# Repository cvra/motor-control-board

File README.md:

CVRA DC-Motor Controller
========================

Features:
---------

 - CAN interface
 - DC motor control with current sensing
 - Quadrature encoder interface for motor (5V tolerant)
 - Secondary quadrature encoder interface (5V tolerant) (eg. for separate odometry wheels)
 - Analog input for RC-servo control
 - Runs on 3 or 4 cell LiPo batteries

License
-------
This project is released under the Creative Commons CC-BY-SA-4.0 license.
See http://creativecommons.org/licenses/by-sa/4.0/ for details.

Assembly
--------

# Applying solder paste

 - This needs 2 persons.
 - Solder paste and stencil need to be _cold_ (couple of minutes in the fridge)
 - Use the 3D printed frames. Stick them to the table with double sided tape
    and stick the PCB to the frame with small pieces of double sided tape.
    If you don't do this, the PCB will stick to the sencil when you try to remove it.
 - To remove the stencil, rotate it around one of the short edges, to pull it
   as perpendicular as possible with the least amount of shaking.
 - Move the PCB with the applied solder paste to a frame without double sided
   tape before assembling the parts, because they would probably flick off.
 - Check the footprints with the smallest pitch under the microscope for bad
   alignment and if the brim is nice (if it isn't, the paste was probably too warm).

# Assembling the parts
 - Remove the solder paste on the NC pad of the voltage regulator with the wrong
   footprint.
 - Use the vacuum pump for larger parts and tweezers for smaller ones.

# Baking

 - Preheat the frame made out of plaster to >200°C, else it won't reflow!
 - Move the PCB to the plaster frame.
 - Put the frame and the thermal probe in the furnace. Take care that you don't
   accidentally move any parts by touching them with the probe.
 - Heat until the solder paste starts to liquidify (shouldn't be more than
   ~230°C; never go higher than 250°C).
 - Keep the peak temperature for about a minute.
 - Open the furnace door a little bit to slowly cool down the PCBs.
 - Don't remove the PCB from the furnace before it's colder than ~70°C.

# Flashing and testing

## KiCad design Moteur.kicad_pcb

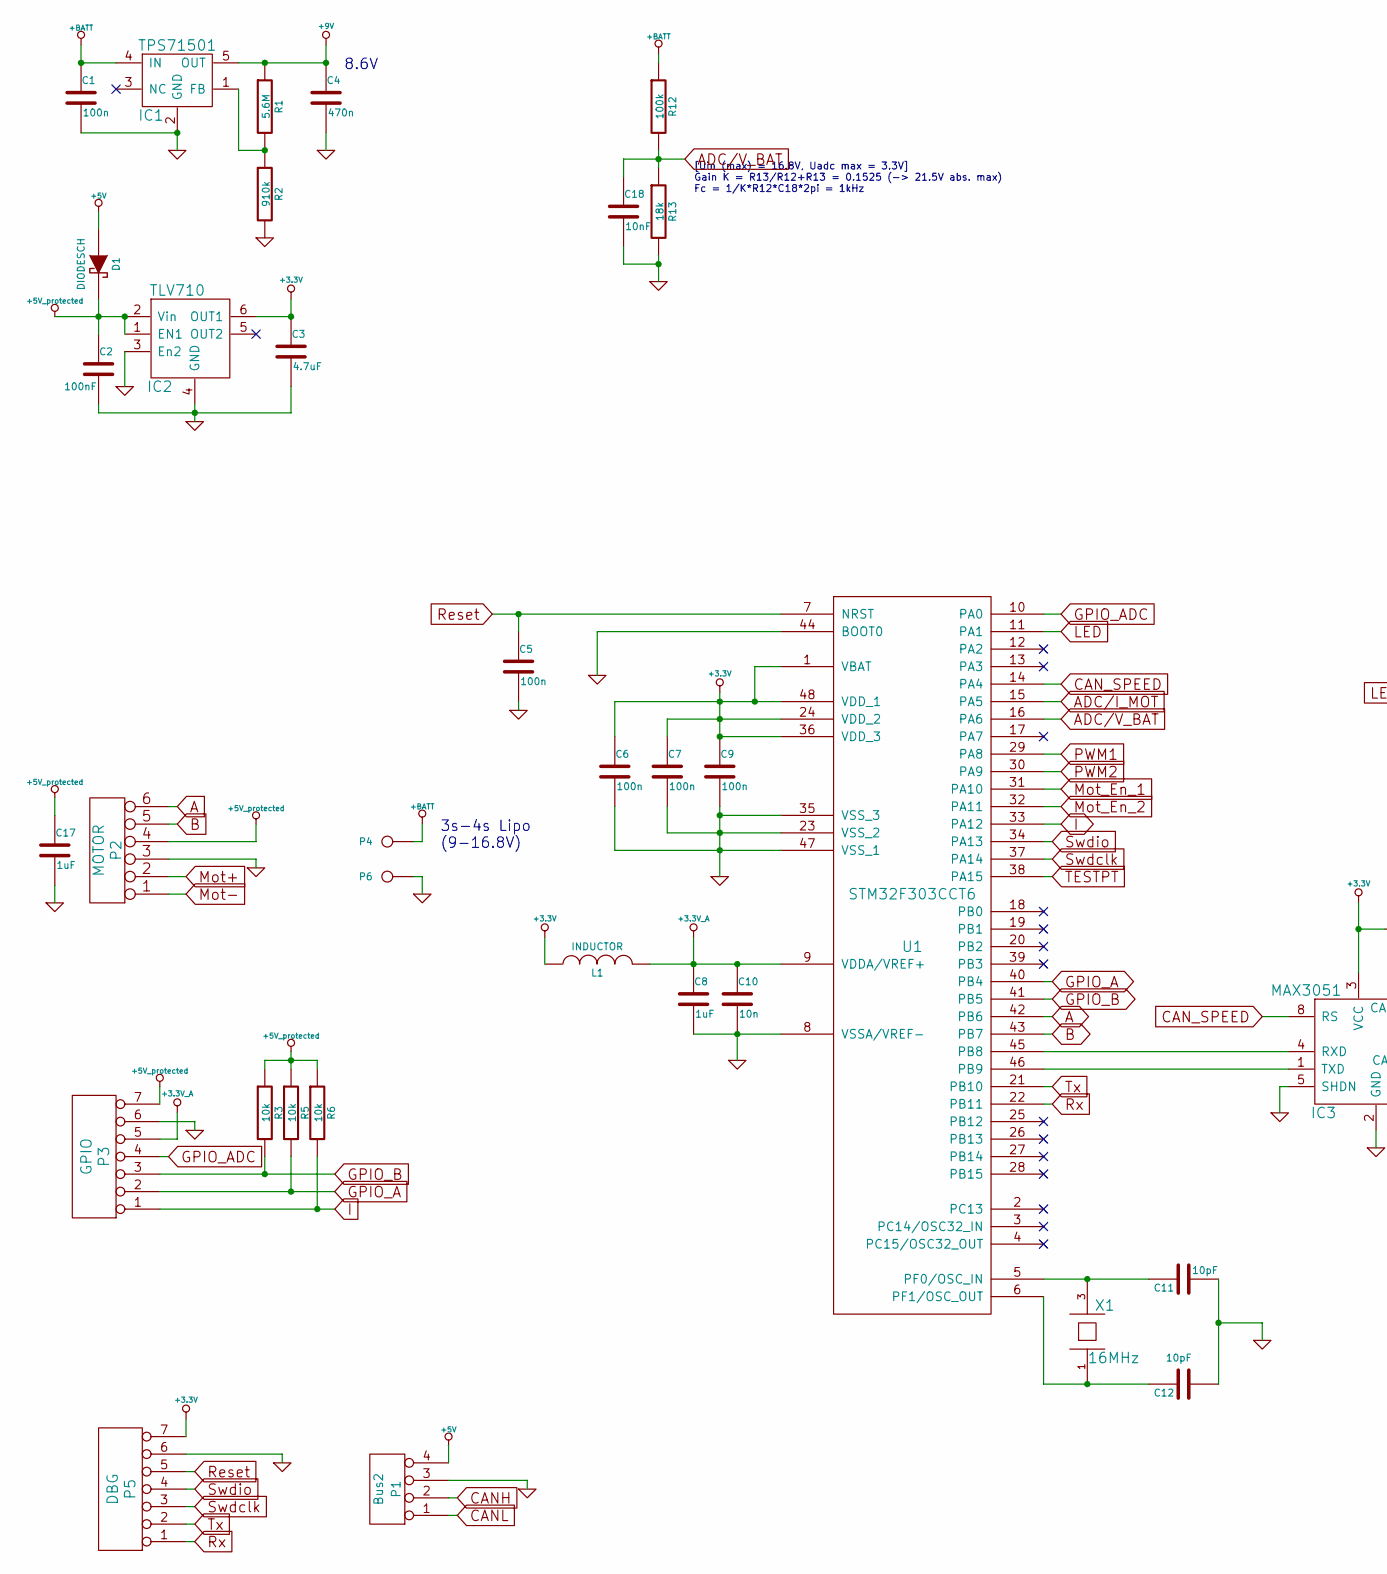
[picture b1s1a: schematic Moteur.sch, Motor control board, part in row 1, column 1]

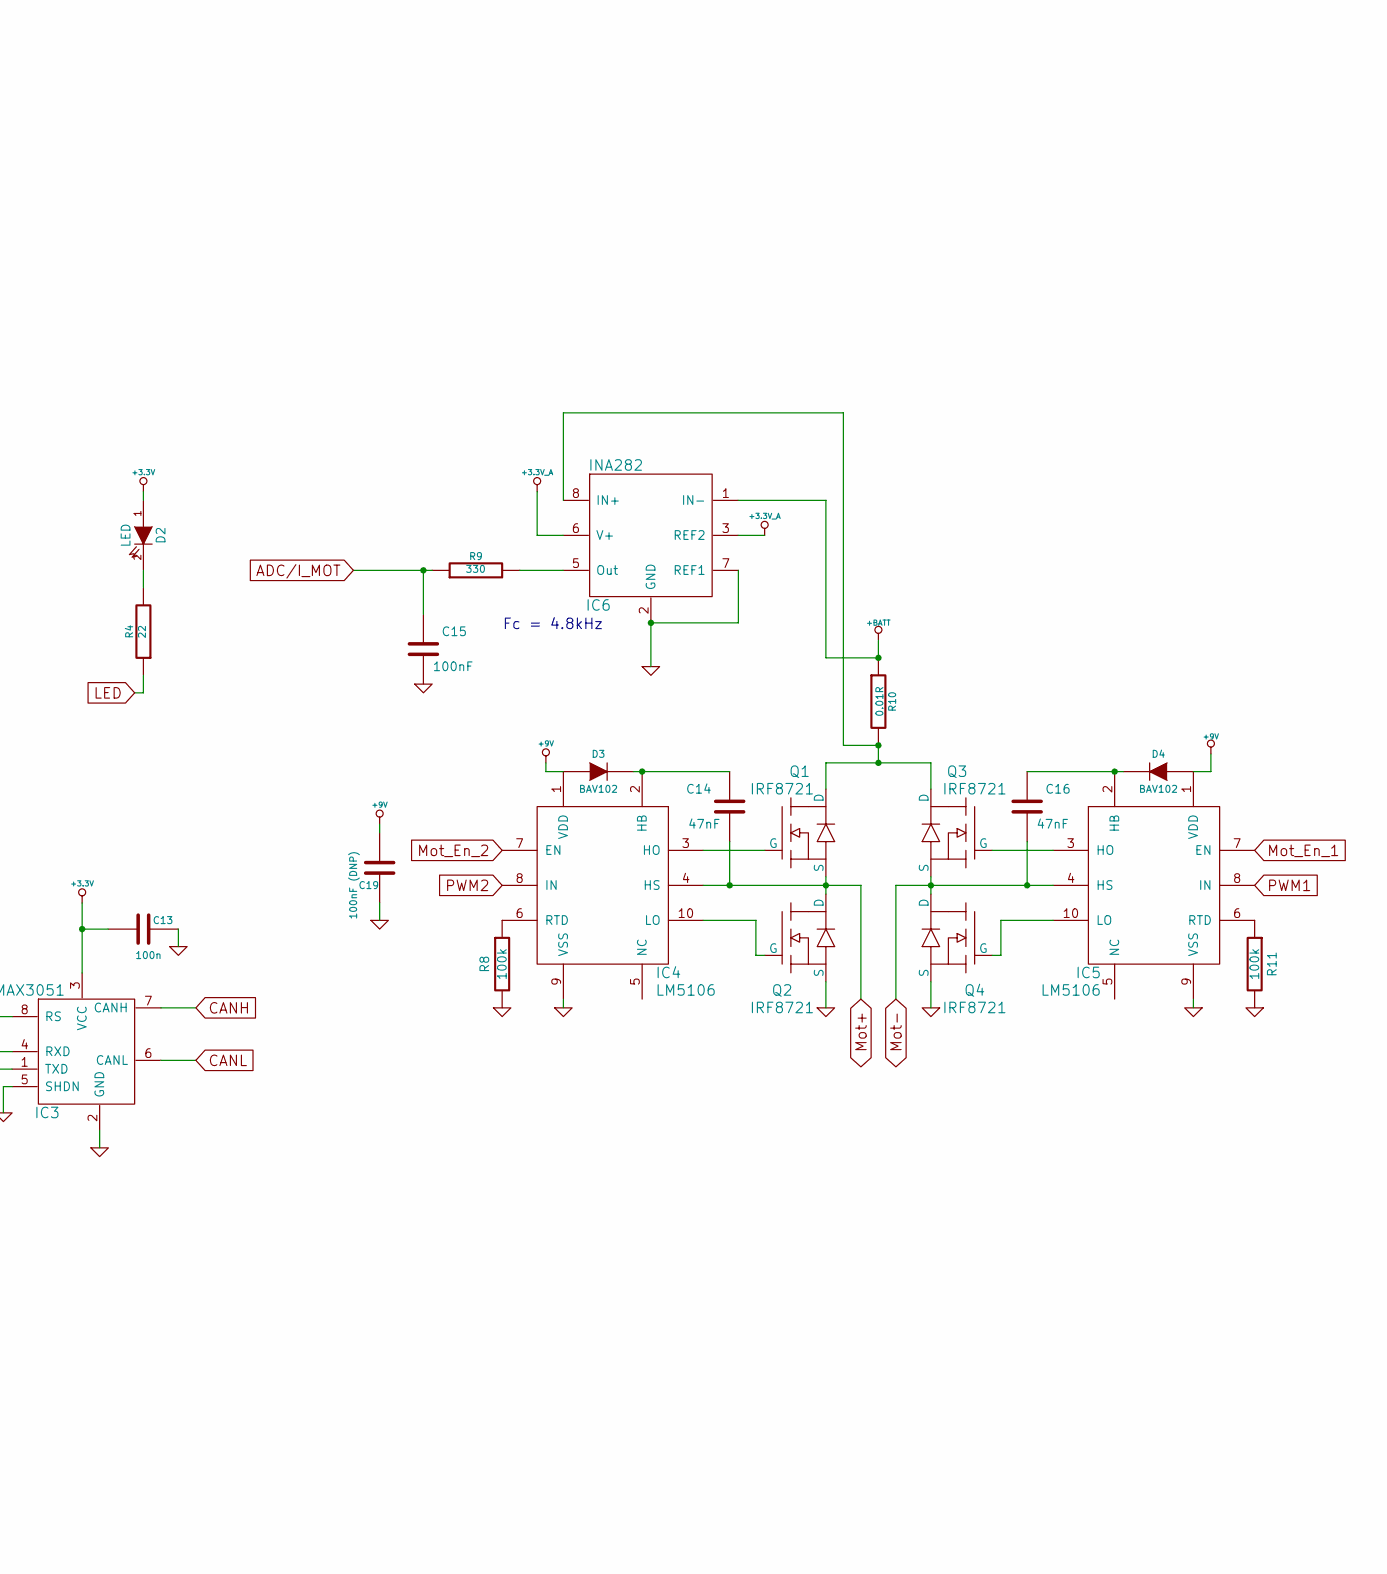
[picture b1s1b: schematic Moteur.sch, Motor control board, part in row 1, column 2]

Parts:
C1, C5, C6, C7, C9, C13: 100n
C2: 100nF
C3: 4.7uF
C4: 470n
C8, C17: 1uF
C10: 10n
C11, C12: 10pF
C14, C16: 47nF; SM1206
C15: 100nF; SM1206
C18: 10nF
C19: 100nF (DNP)
D1: DIODESCH
D2: LED
D3, D4: BAV102; diode-1-SOD80C
IC1: TPS71501
IC2: TLV710
IC3: MAX3051
IC4, IC5: LM5106
IC6: INA282
L1: INDUCTOR
P1: Bus2
P2: MOTOR
P3: GPIO
P4, P6: CONN_1
P5: DBG
Q1, Q2, Q3, Q4: IRF8721; transistor-power-SOT669
R1: 5.6M
R2: 910k
R3, R5, R6: 10k
R4: 22
R8, R11: 100k; SM0805
R9: 330
R10: 0.01R
R12: 100k
R13: 18k
U1: STM32F303CCT6; MODULE
X1: 16MHz

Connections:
+3.3V: C3.1, C6.1, C7.1, C9.1, C13.2, D2.1 (A), IC2.6 (OUT1), IC3.3 (VCC), L1.1, P5.7, U1.1 (VBAT), U1.24 (VDD_2), U1.36 (VDD_3), U1.48 (VDD_1)
+3.3V_A: C8.1, C10.1, IC6.3 (REF2), IC6.6 (V+), L1.2, P3.5, U1.9 (VDDA/VREF+)
+5V: D1.1 (A), P1.4
+5V_protected: C2.1, C17.1, D1.2 (K), IC2.1 (EN1), IC2.2 (Vin), P2.4, P3.7, R3.1, R5.1, R6.1
+9V: C4.1, C19.2, D3.1 (A), D4.1 (A), IC1.5 (OUT), IC4.1 (VDD), IC5.1 (VDD), R1.1
+BATT: C1.1, IC1.4 (IN), IC6.1 (IN-), P4.1, R10.1, R12.1
A: P2.6, U1.42 (PB6)
ADC/I_MOT: C15.1, R9.1, U1.15 (PA5)
ADC/V_BAT: C18.1, R12.2, R13.1, U1.16 (PA6)
B: P2.5, U1.43 (PB7)
CANH: IC3.7 (CANH), P1.2
CANL: IC3.6 (CANL), P1.1
CAN_SPEED: IC3.8 (RS), U1.14 (PA4)
GND: C1.2, C2.2, C3.2, C4.2, C5.2, C6.2, C7.2, C8.2, C9.2, C10.2, C11.2, C12.2, C13.1, C15.2, C17.2, C18.2, C19.1, IC1.2 (GND), IC2.3 (En2), IC2.4 (GND), IC3.2 (GND), IC3.5 (SHDN), IC4.9 (VSS), IC5.9 (VSS), IC6.2 (GND), IC6.7 (REF1), P1.3, P2.3, P3.6, P5.6, P6.1, Q2.1 (S), Q2.2, Q2.3, Q4.1 (S), Q4.2, Q4.3, R2.2, R8.2, R11.2, R13.2, U1.8 (VSSA/VREF-), U1.23 (VSS_2), U1.35 (VSS_3), U1.44 (BOOT0), U1.47 (VSS_1)
GPIO_A: P3.2, R5.2, U1.40 (PB4)
GPIO_ADC: P3.4, U1.10 (PA0)
GPIO_B: P3.3, R3.2, U1.41 (PB5)
I: P3.1, R6.2, U1.33 (PA12)
LED: R4.1, U1.11 (PA1)
Mot+: C14.2, IC4.4 (HS), P2.2, Q1.1 (S), Q1.2, Q1.3, Q2.5 (D), Q2.6, Q2.7, Q2.8
Mot-: C16.2, IC5.4 (HS), P2.1, Q3.1 (S), Q3.2, Q3.3, Q4.5 (D), Q4.6, Q4.7, Q4.8
Mot_En_1: IC5.7 (EN), U1.31 (PA10)
Mot_En_2: IC4.7 (EN), U1.32 (PA11)
unnamed: C11.1, U1.5 (PF0/OSC_IN), X1.3
unnamed: C12.1, U1.6 (PF1/OSC_OUT), X1.1
unnamed: C14.1, D3.2 (K), IC4.2 (HB)
unnamed: C16.1, D4.2 (K), IC5.2 (HB)
unnamed: D2.2 (K), R4.2
unnamed: IC1.1 (FB), R1.2, R2.1
unnamed: IC3.1 (TXD), U1.46 (PB9)
unnamed: IC3.4 (RXD), U1.45 (PB8)
unnamed: IC4.3 (HO), Q1.4 (G)
unnamed: IC4.6 (RTD), R8.1
unnamed: IC4.10 (LO), Q2.4 (G)
unnamed: IC5.3 (HO), Q3.4 (G)
unnamed: IC5.6 (RTD), R11.1
unnamed: IC5.10 (LO), Q4.4 (G)
unnamed: IC6.5 (Out), R9.2
unnamed: IC6.8 (IN+), Q1.5 (D), Q1.6, Q1.7, Q1.8, Q3.5 (D), Q3.6, Q3.7, Q3.8, R10.2
PWM1: IC5.8 (IN), U1.29 (PA8)
PWM2: IC4.8 (IN), U1.30 (PA9)
Reset: C5.1, P5.5, U1.7 (NRST)
Rx: P5.1, U1.22 (PB11)
Swdclk: P5.3, U1.37 (PA14)
Swdio: P5.4, U1.34 (PA13)
TESTPT: U1.38 (PA15)
Tx: P5.2, U1.21 (PB10)

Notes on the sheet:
Fc = 4.8kHz
[Uin (max) = 16.8V, Uadc max = 3.3V] Gain K = R13/R12+R13 = 0.1525 (-> 21.5V abs. max) Fc = 1/K*R12*C18*2pi = 1kHz
3s-4s Lipo (9-16.8V)
8.6V

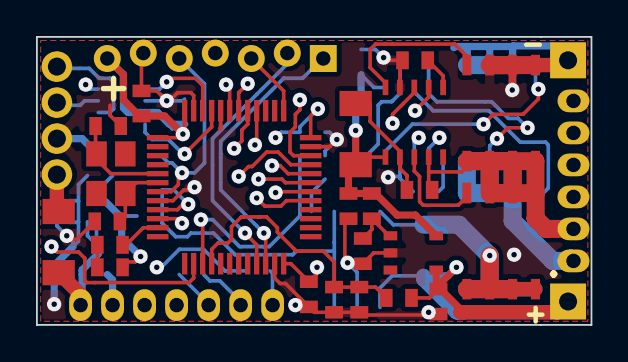
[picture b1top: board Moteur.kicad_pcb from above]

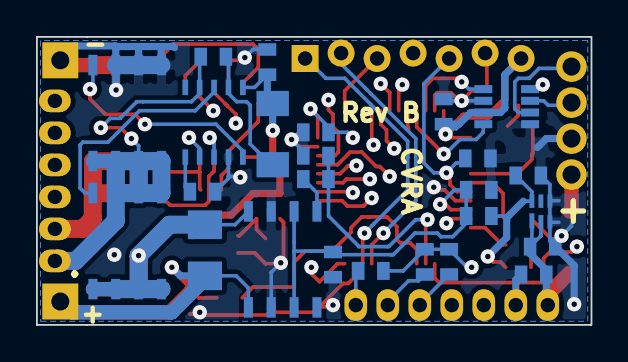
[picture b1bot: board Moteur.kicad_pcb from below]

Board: 4 copper layers, 30.8 x 16.0 mm, 54 parts (26 on the bottom side), 46 nets.

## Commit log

2014-10-31 add kicad lib submodule
2014-10-31 add cache
2014-10-31 gitignore
2014-10-31 add all libs
2014-10-31 add correct stm32 symbol
2014-10-31 add pinout
2014-11-05 design review
2014-11-05 update submodule url
2014-11-05 update library path
2014-11-05 Add something useless
2014-11-05 remove something useless
2014-11-05 Update the library with the most beautiful symbol EVER EVER EVER !
2014-11-05 update current measurement filter, fix connection CAN termination resistor
2014-11-05 power supply minor fixes
2014-11-09 Schéma Complet
2014-11-10 Add datasheet folder
2014-11-12 Couche PCB Définie
2014-11-13 minor schematic fixes, start assigning footprints
2014-11-13 footprints assignment
2014-11-13 connect encoders to diode protected 5V
2014-11-13 add V_Bat resistive divider for ADC
2014-11-13 remove nonexistent libs, add cvra lib
2014-11-13 Fix 5V protected symbol name
    Apparently KiCAD has case sensitive symbol names... nice
2014-11-13 change submodule from ssh to https
2014-11-15 Add Diode
2014-11-15 Boitier Choisi
2014-11-16 Set footprint for TLV710 and LM5106 Corrected footprint for shunt resistor
2014-11-19 update lib
2014-11-19 footprints
2014-11-22 Update footprint link, disperse component on PCB and add pcb size
2014-11-23 Add board outline and placed power stage
2014-11-23 Placement driver can
2014-11-26 fix labels, pinout
2014-11-26 final schematic review, component placement
2014-11-27 placement
2014-11-27 component placement
2014-11-28 add GND to GPIO connector, exchange CANL,CANH
2014-11-28 optimize placement
2014-11-28 add new gpio connector with gnd
2014-12-02 start routing
2014-12-03 exchange shunt resistance pins
2014-12-03 routing, exchanged shunt resistor pins
2014-12-03 routing
2014-12-03 routing (power)
2014-12-05 routing, almost done
2014-12-06 routing, changed connectors
2014-12-06 update debug connector footprint
2014-12-08 update connector, thermal for connectors
2014-12-08 Battery gnd thermal
2014-12-08 gnd via
2014-12-08 silkscreen
2014-12-08 add schematic pdf
2014-12-10 Gerber fabrication output.
2014-12-10 readme & pcb preview
2014-12-11 Add license (fixed #1)
2015-01-03 resistive divider values & schematic annotations
2015-01-03 add BOM
2015-01-30 Update library to get 3d models
2015-01-30 Place 3d models on PCB and export in VRML format
2015-01-30 Add pictures of 3d preview
2015-01-30 Revert "Add pictures of 3d preview"
    This reverts commit 0d437f94a2021f2fa19f4f4f6cde7e7ec32b1b53.
2015-01-30 Revert "Place 3d models on PCB and export in VRML format"
    This reverts commit 3c79a8abd9414d5cc485e12aba148d6700e70ad2.
2015-01-30 Fixing some 3d model issues
2015-01-30 Update 3d pictures
2015-01-31 move imgages to subfolder
2015-01-31 clean up datasheets
2015-02-01 Update 3d model with components on PCB embedded in VRML
2015-02-01 Update VRML 3d model of PCB
2015-02-02 Checkout library at right commit
2015-02-06 remove RGB-led datasheet
2015-02-06 fix current amplifier common mode issue
2015-02-06 add pdf schematic
2015-02-06 revB silkscreen
2015-02-06 optimize GND
2015-02-14 document limitations of Rev A
2015-04-08 started writing an assembly guide
2015-04-11 correct LED resistor
2015-04-14 important note to the baking process
2018-02-22 Document voltage regulator issue
